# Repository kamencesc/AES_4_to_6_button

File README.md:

# Not tested yet

# AES 4 to 6 button
A board to use a 4 button AES stick/gamepad on to a Supergun with a DB15 6 button layout.

It uses a ATtiny84 for the logic and then send the correct button push to the Supergun.

The code uses by default this config:

A = Light Punch
B = Heavy Punch
A + B = Middle Punch
C = Light Kick
D = Heavy Kick
C + D = Middle Kick

Feel free to modify to adapt at your own preferences.

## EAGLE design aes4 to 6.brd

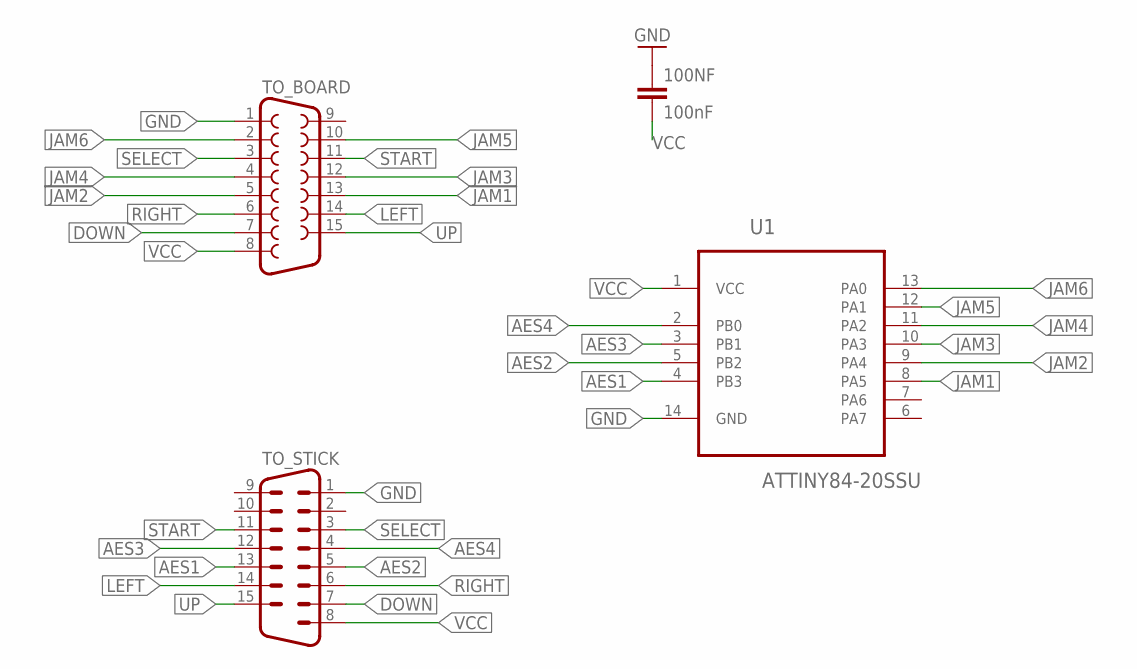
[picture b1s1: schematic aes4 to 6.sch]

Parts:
100NF: 100nF; 0603
TO_BOARD: F15D
TO_STICK: M15D
U1: ATTINY84-20SSU; SOIC127P600X175-14N

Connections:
AES1: TO_STICK.13, U1.4 (PB3)
AES2: TO_STICK.5, U1.5 (PB2)
AES3: TO_STICK.12, U1.3 (PB1)
AES4: TO_STICK.4, U1.2 (PB0)
DOWN: TO_BOARD.7, TO_STICK.7
GND: 100NF.1, TO_BOARD.1, TO_STICK.1, U1.14 (GND)
JAM1: TO_BOARD.13, U1.8 (PA5)
JAM2: TO_BOARD.5, U1.9 (PA4)
JAM3: TO_BOARD.12, U1.10 (PA3)
JAM4: TO_BOARD.4, U1.11 (PA2)
JAM5: TO_BOARD.10, U1.12 (PA1)
JAM6: TO_BOARD.2, U1.13 (PA0)
LEFT: TO_BOARD.14, TO_STICK.14
RIGHT: TO_BOARD.6, TO_STICK.6
SELECT: TO_BOARD.3, TO_STICK.3
START: TO_BOARD.11, TO_STICK.11
UP: TO_BOARD.15, TO_STICK.15
VCC: 100NF.2, TO_BOARD.8, TO_STICK.8, U1.1 (VCC)

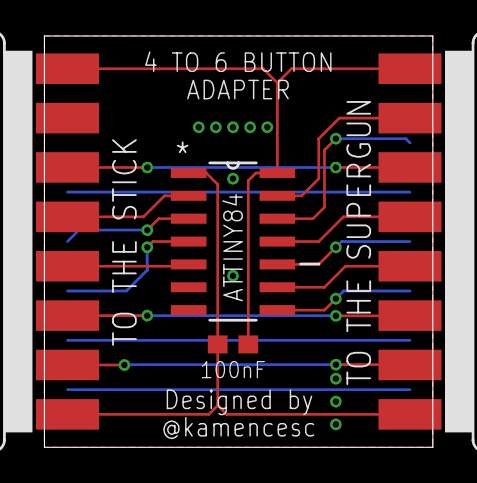
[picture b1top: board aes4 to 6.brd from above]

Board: 2 copper layers, 21.6 x 22.9 mm, 4 parts (0 on the bottom side), 18 nets.

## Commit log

2019-07-01 Fist version
    First versión of board and code

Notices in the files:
parts and their libraries:
SparkFun-Capacitors: Licensing: Creative Commons ShareAlike 4.0 International - https://creativecommons.org/licenses/by-sa/4.0
